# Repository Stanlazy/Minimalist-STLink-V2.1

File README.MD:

# Minimalist-STLink-V2.1

Solderjump on the back should be disconnected for jlink firmware, connected when used with stlink firmware

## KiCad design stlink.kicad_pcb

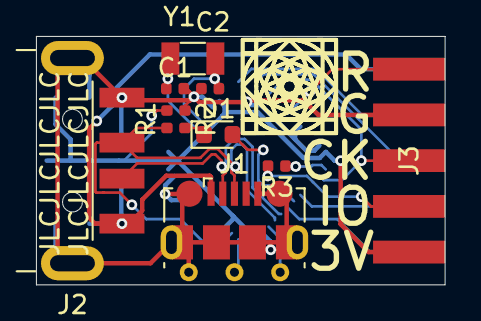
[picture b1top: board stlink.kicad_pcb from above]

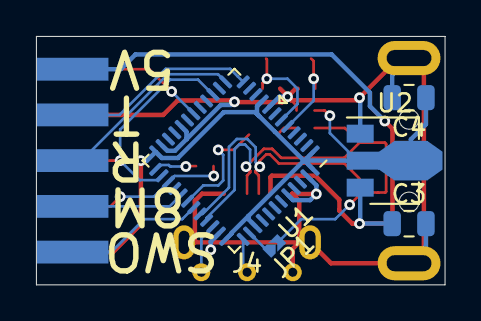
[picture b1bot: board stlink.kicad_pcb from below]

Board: 2 copper layers, 22.7 x 13.8 mm, 16 parts (6 on the bottom side), 20 nets.

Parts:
C1, C2: C; C_0402_1005Metric
C3, C4: C; C_0805_2012Metric
D1: LED; LED_0603_1608Metric
J1: USB_B_Micro; USB_Micro-B_Molex-105017-0001
J2: USB_A; USB_A_CNCTech_1001-011-01101_Horizontal
J3: Conn_02x05_Counter_Clockwise; PinHeader_2x05_P2.54mm_PCBEdge
J4: Conn_01x03_Female; TP_SWD_3pin_2.54mm
JP1: Jumper; SolderJumper-2_P0.7mm
R1: 1.5k; R_0402_1005Metric
R2: R; R_0402_1005Metric
R3: 100R; R_0402_1005Metric
U1: STM32F103CBUx; QFN-48-1EP_7x7mm_P0.5mm_EP5.6x5.6mm
U2: LM1117-3.3; SOT-89-3
Y1: Crystal; Crystal_SMD_3215-2Pin_3.2x1.5mm

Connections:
+3V3: C4.1, J3.5, R1.2, U1.1, U1.9, U1.24, U1.36, U1.39, U1.48, U2.2
+5V: C3.1, J1.1, J2.1, J3.10, U2.3
GND: C1.2, C2.2, C3.2, C4.2, J1.5, J1.6, J2.4, J2.5, J3.2, J4.1, R2.1, U1.8, U1.20, U1.23, U1.35, U1.44, U1.47, U2.1
LED_STA: D1.2, U1.30
L_SWCLK: J4.2, U1.37
L_SWDIO: J4.3, U1.34
MCO: J3.7, U1.29
unnamed: C1.1, U1.5, Y1.1
unnamed: C2.1, U1.6, Y1.2
unnamed: D1.1, R2.2
unnamed: JP1.1, U1.38
unnamed: R3.1, U1.25
RX: J3.8, U1.13
TX: J3.9, U1.12
T_JTCK: J3.3, U1.15, U1.26
T_JTMS: J3.4, R3.2, U1.27
T_SWO: J3.6, U1.31
T_nRST: J3.1, U1.18
USB_N: J1.2, J2.2, U1.32
USB_P: J1.3, J2.3, JP1.2, R1.1, U1.33

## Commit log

2020-10-25 added readme
2020-10-25 hmmm
